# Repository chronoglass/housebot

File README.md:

# housebot
Plan is a roving tracked bot with hardpoints for mounting equipment/sensors or other bots.

l1 goals:
Tracked chassis with build in battery failsafes and compartments for "brains"

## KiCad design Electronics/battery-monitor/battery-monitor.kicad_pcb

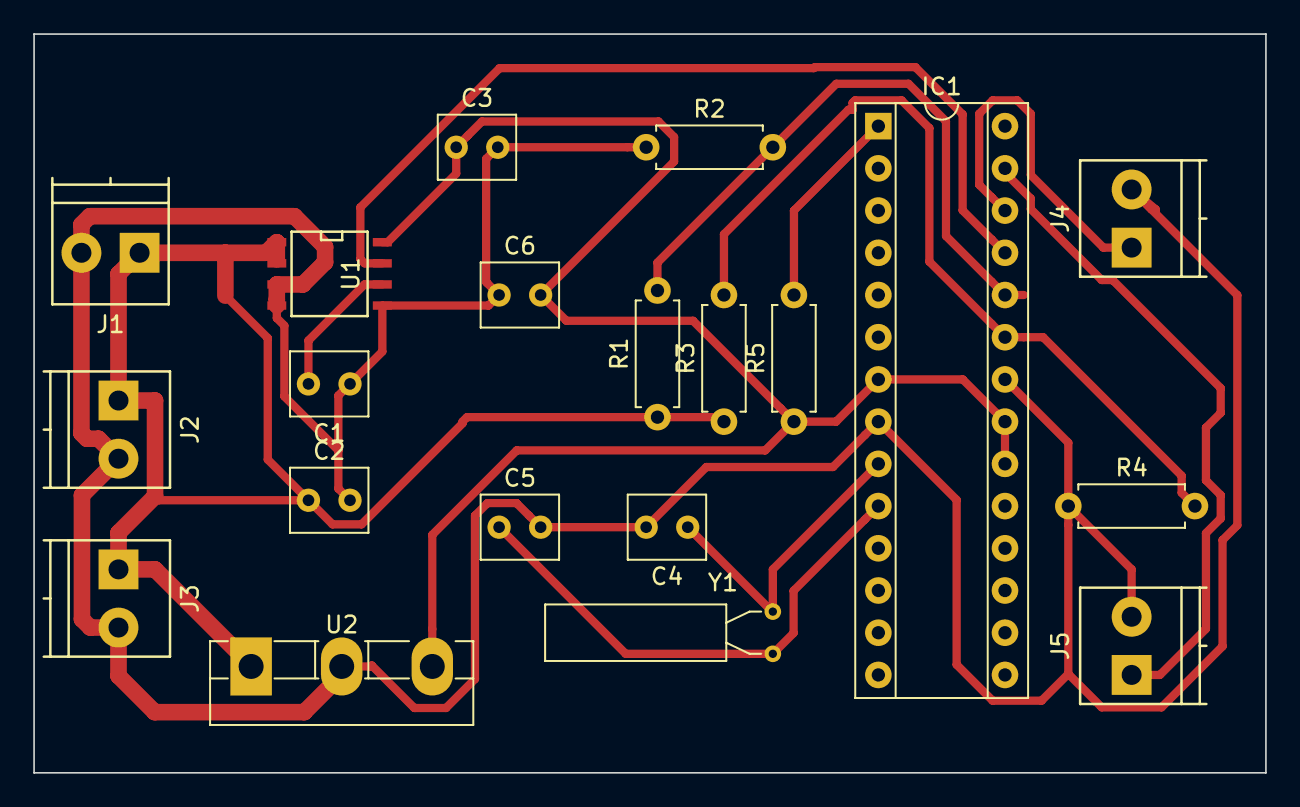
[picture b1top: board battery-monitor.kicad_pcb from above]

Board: 2 copper layers, 74.1 x 44.5 mm, 20 parts (0 on the bottom side), 12 nets.

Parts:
C1, C2, C3, C4, C5, C6: C; C_Rect_L4.6mm_W3.8mm_P2.50mm_MKS02_FKP02
IC1: ATMEGA328P-P; DIP-28_W7.62mm_Socket
J1, J2, J3, J4, J5: Screw_Terminal_1x02; TerminalBlock_Pheonix_PT-3.5mm_2pol
R1, R2, R3, R4, R5: R; R_Axial_DIN0207_L6.3mm_D2.5mm_P7.62mm_Horizontal
U1: ACS714LLCTR-30A-T; SOIC-8-N
U2: LM7805CT; TO-3PB__Vertical
Y1: Crystal; Crystal_AT310_d3.0mm_l10.0mm_Horizontal

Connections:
unnamed: C1.1, C2.2, C3.2, C4.2, C5.2, C6.1, IC1.8, IC1.22, J1.2, J2.2, J3.2, J4.2, J5.2, R2.1, R4.1, U1.3, U1.4, U1.5, U2.2
unnamed: C1.2, U1.6
unnamed: C2.1, J1.1, J2.1, J3.1, R1.1, R3.1, U1.1, U1.2, U2.1
unnamed: C3.1, C6.2, IC1.7, IC1.20, IC1.21, R5.1, U1.8, U2.3
unnamed: C4.1, IC1.9, Y1.1
unnamed: C5.1, IC1.10, Y1.2
unnamed: IC1.1, R5.2
unnamed: IC1.23, R3.2, R4.2
unnamed: IC1.24, R1.2, R2.2
unnamed: IC1.25, U1.7
unnamed: IC1.26, J4.1
unnamed: IC1.27, J5.1

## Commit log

2017-05-29 power control unit semi scrapped, battery monitor 60%
2017-05-29 added gitignore to remove dirs named extra
2017-05-29 cleanup
2017-05-29 base layout done, freeroute files exported
2017-05-29 svg created, fighting with various cam software to get my process down
2017-05-29 svg created, fighting with various cam software to get my process down. take2
2017-06-05 board changed to add ATMEGA for onboard monitoring
2017-06-05 new cut using pcb2gcode
2017-06-05 adjusting speeds
2017-06-25 cleaned up board files and finally made a successful cut on the battery monitor
2017-06-25 board folder left out
2017-06-25 added pcb2gcode settings used for cut
2017-06-25 warning battery monitor board
